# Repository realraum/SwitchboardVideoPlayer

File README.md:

# Switchboard Video Player

Use a manual telephone switchboard to select videos shown on a screen in a museum for example

## Sources:

https://github.com/labtroll/KiCad-DesignRules

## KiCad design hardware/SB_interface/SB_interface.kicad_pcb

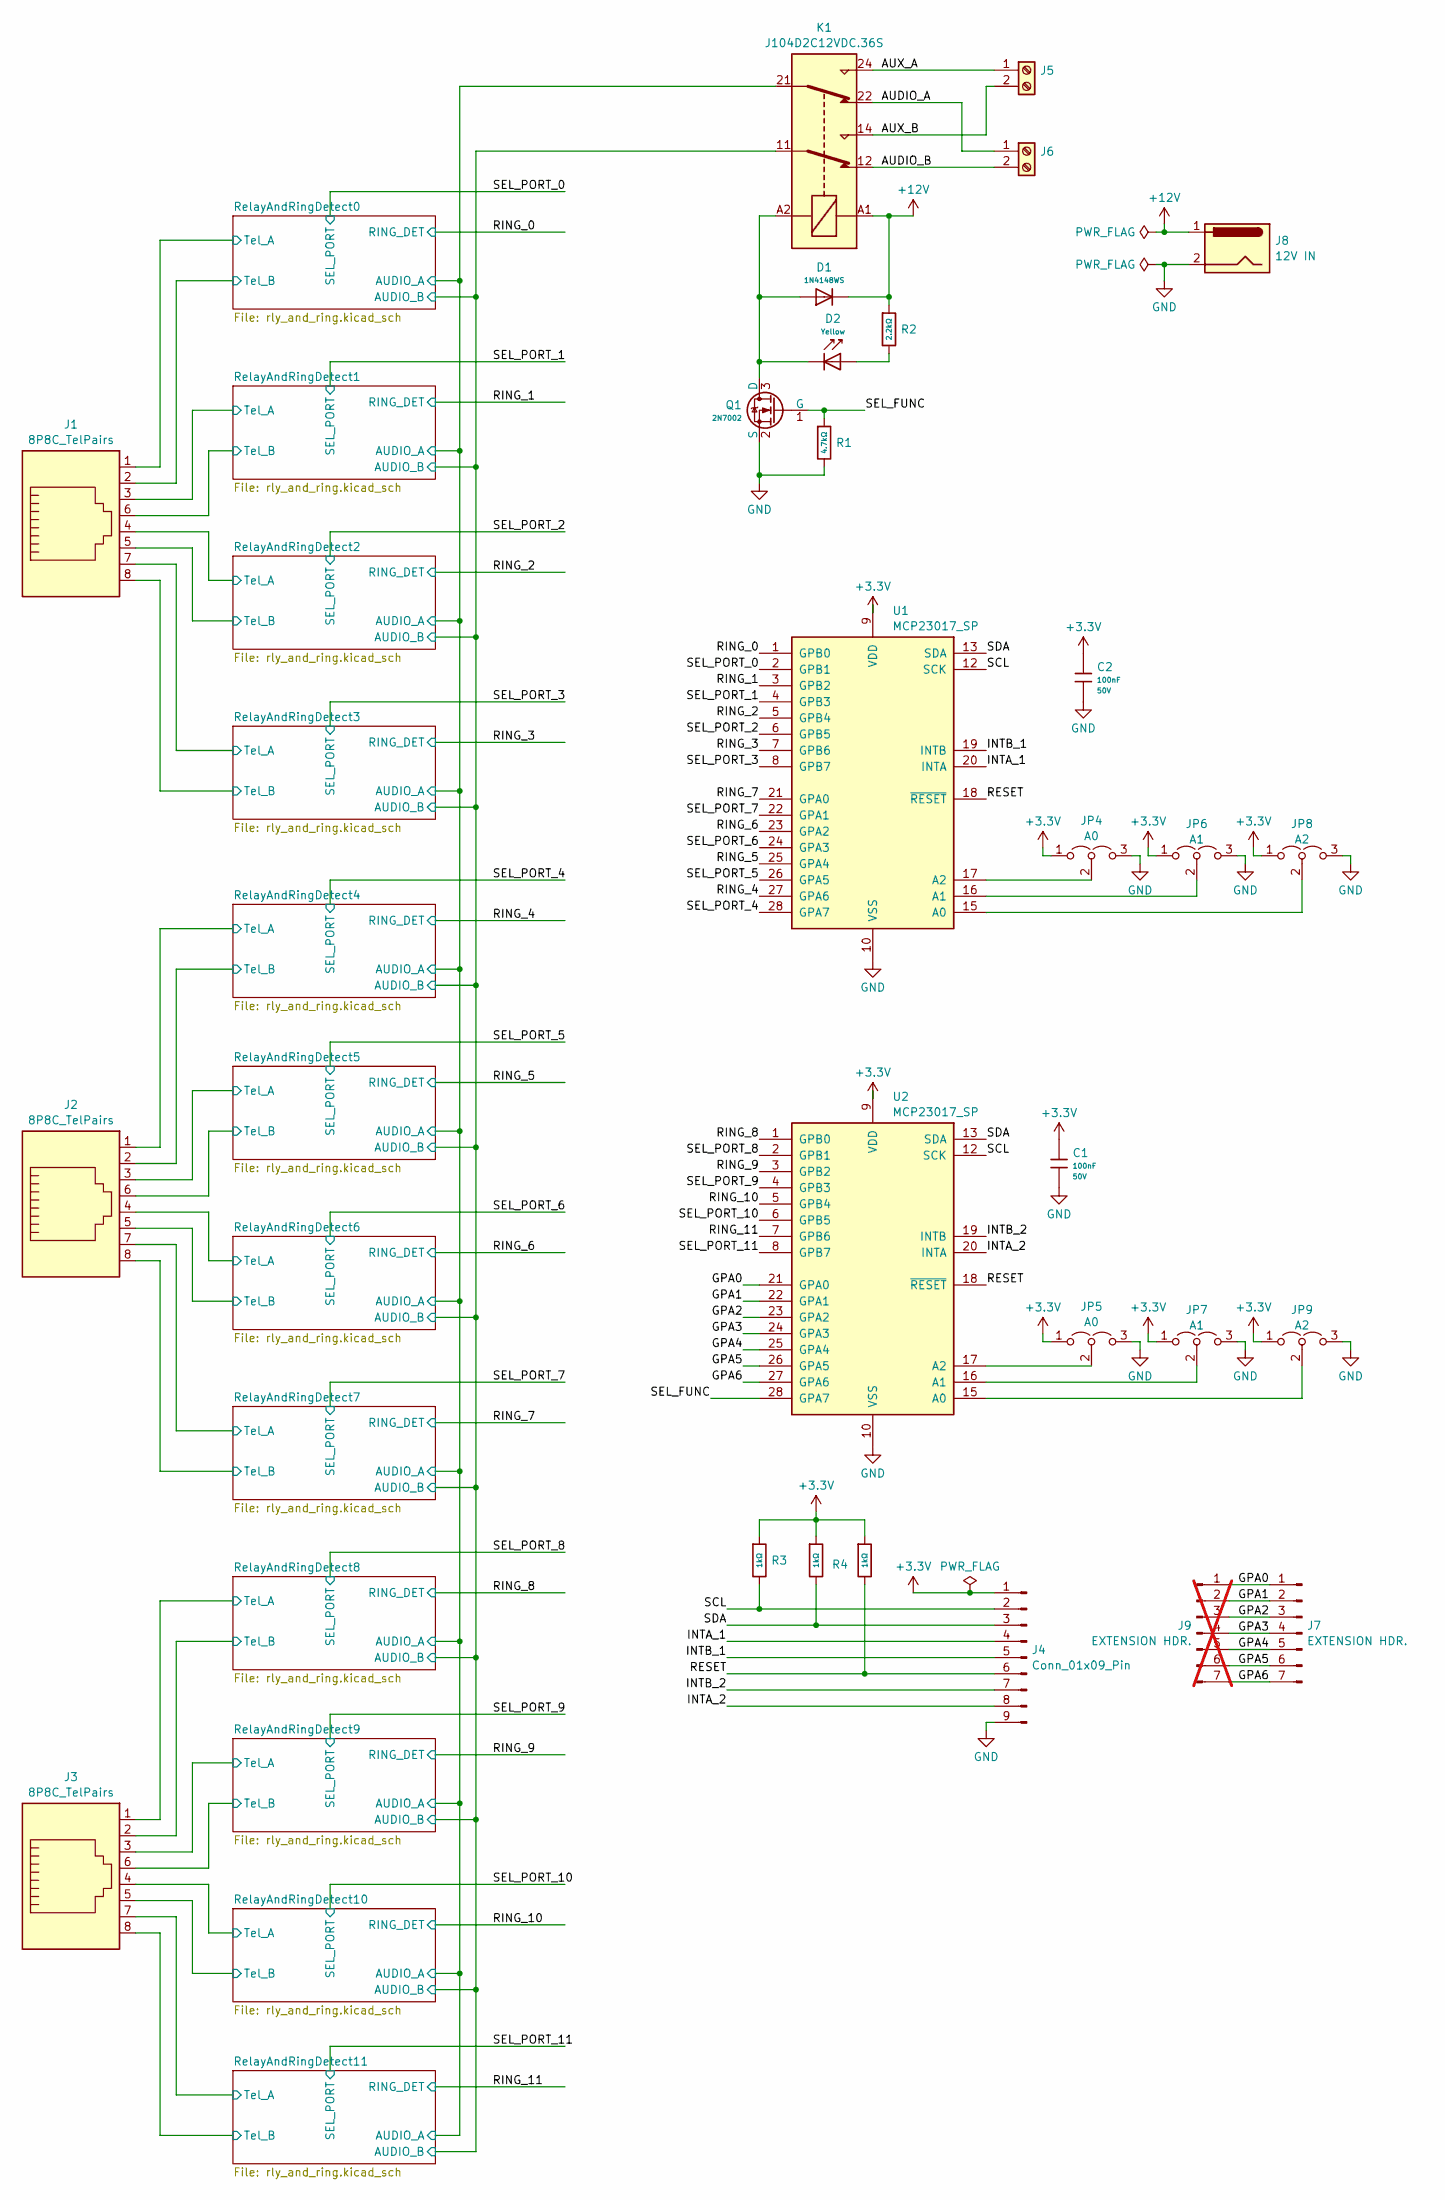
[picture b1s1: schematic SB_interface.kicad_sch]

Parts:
C1, C2: 100nF; C_0805; Voltage Rated 50V; Tolerance ±10%; Part CC0805KRX7R9BB104; LCSC C49678
D1: 1N4148WS; D_SOD-323; Forward Voltage (Vf@If) 1.25V@150mA; Reverse Voltage (Vr) 100V; Part 1N4148WS; LCSC C2128
D2: Yellow; D_0805; Part KT-0805Y; LCSC C2296
J1, J2, J3: 8P8C_TelPairs; RJ45_Amphenol_54602-x08_Horizontal
J4: Conn_01x09_Pin; PinHeader_1x09_P2.54mm_Vertical
J5: AUX; TerminalBlock_Phoenix_PT-1,5-2-3.5-H_1x02_P3.50mm_Horizontal
J6: AUDIO; TerminalBlock_Phoenix_PT-1,5-2-3.5-H_1x02_P3.50mm_Horizontal
J7: EXTENSION HDR.; PinHeader_1x07_P2.54mm_Vertical
J8: 12V IN; BarrelJack_Horizontal
J9: EXTENSION HDR.; PinHeader_1x07_P2.54mm_Vertical; not fitted
JP4, JP5: A0; PinHeader_1x03_P2.54mm_Vertical
JP6, JP7: A1; PinHeader_1x03_P2.54mm_Vertical
JP8, JP9: A2; PinHeader_1x03_P2.54mm_Vertical
K1: J104D2C12VDC.36S
Q1: 2N7002; Q_SOT-23; Part 2N7002; LCSC C8545
R1: 4.7kΩ; R_0805; Overload Voltage (Max) 150V; Tolerance ±1%; Part 0805W8F4701T5E; LCSC C17673
R2: 2.2kΩ; R_0805; Overload Voltage (Max) 150V; Tolerance ±1%; Part 0805W8F2201T5E; LCSC C17520
R3, R4, R5: 1kΩ; R_0805; Overload Voltage (Max) 150V; Tolerance ±1%; Part 0805W8F1001T5E; LCSC C17513
U1, U2: MCP23017_SP; DIP-28_W7.62mm

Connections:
+3.3V: C1.1, C2.1, J4.1, JP4.1 (A), JP5.1 (A), JP6.1 (A), JP7.1 (A), JP8.1 (A), JP9.1 (A), R3.1, R4.1, R5.1, U1.9 (VDD), U2.9 (VDD); also elsewhere on the board
+12V: D1.1, J8.1, K1.A1, R2.1; also elsewhere on the board
/AUDIO_A: J6.1, K1.22
/AUDIO_B: J6.2, K1.12
/AUX_A: J5.1, K1.24
/AUX_B: J5.2, K1.14
/GPA0: J7.1, J9.1, U2.21 (GPA0)
/GPA1: J7.2, J9.2, U2.22 (GPA1)
/GPA2: J7.3, J9.3, U2.23 (GPA2)
/GPA3: J7.4, J9.4, U2.24 (GPA3)
/GPA4: J7.5, J9.5, U2.25 (GPA4)
/GPA5: J7.6, J9.6, U2.26 (GPA5)
/GPA6: J7.7, J9.7, U2.27 (GPA6)
/INTA_1: J4.4, U1.20 (INTA)
/INTA_2: J4.8, U2.20 (INTA)
/INTB_1: J4.5, U1.19 (INTB)
/INTB_2: J4.7, U2.19 (INTB)
/RESET: J4.6, R5.2, U1.18 (~RESET), U2.18 (~RESET)
/RING_0: U1.1 (GPB0); also elsewhere on the board
/RING_1: U1.3 (GPB2); also elsewhere on the board
/RING_2: U1.5 (GPB4); also elsewhere on the board
/RING_3: U1.7 (GPB6); also elsewhere on the board
/RING_4: U1.27 (GPA6); also elsewhere on the board
/RING_5: U1.25 (GPA4); also elsewhere on the board
/RING_6: U1.23 (GPA2); also elsewhere on the board
/RING_7: U1.21 (GPA0); also elsewhere on the board
/RING_8: U2.1 (GPB0); also elsewhere on the board
/RING_9: U2.3 (GPB2); also elsewhere on the board
/RING_10: U2.5 (GPB4); also elsewhere on the board
/RING_11: U2.7 (GPB6); also elsewhere on the board
/RelayAndRingDetect0/AUDIO_A: K1.21; also elsewhere on the board
/RelayAndRingDetect0/AUDIO_B: K1.11; also elsewhere on the board
/RelayAndRingDetect0/Tel_A: J1.1; also elsewhere on the board
/RelayAndRingDetect0/Tel_B: J1.2; also elsewhere on the board
/RelayAndRingDetect1/Tel_A: J1.3; also elsewhere on the board
/RelayAndRingDetect1/Tel_B: J1.6; also elsewhere on the board
/RelayAndRingDetect2/Tel_A: J1.4; also elsewhere on the board
/RelayAndRingDetect2/Tel_B: J1.5; also elsewhere on the board
/RelayAndRingDetect3/Tel_A: J1.7; also elsewhere on the board
/RelayAndRingDetect3/Tel_B: J1.8; also elsewhere on the board
/RelayAndRingDetect4/Tel_A: J2.1; also elsewhere on the board
/RelayAndRingDetect4/Tel_B: J2.2; also elsewhere on the board
/RelayAndRingDetect5/Tel_A: J2.3; also elsewhere on the board
/RelayAndRingDetect5/Tel_B: J2.6; also elsewhere on the board
/RelayAndRingDetect6/Tel_A: J2.4; also elsewhere on the board
/RelayAndRingDetect6/Tel_B: J2.5; also elsewhere on the board
/RelayAndRingDetect7/Tel_A: J2.7; also elsewhere on the board
/RelayAndRingDetect7/Tel_B: J2.8; also elsewhere on the board
/RelayAndRingDetect8/Tel_A: J3.1; also elsewhere on the board
/RelayAndRingDetect8/Tel_B: J3.2; also elsewhere on the board
/RelayAndRingDetect9/Tel_A: J3.3; also elsewhere on the board
/RelayAndRingDetect9/Tel_B: J3.6; also elsewhere on the board
/RelayAndRingDetect10/Tel_A: J3.4; also elsewhere on the board
/RelayAndRingDetect10/Tel_B: J3.5; also elsewhere on the board
/RelayAndRingDetect11/Tel_A: J3.7; also elsewhere on the board
/RelayAndRingDetect11/Tel_B: J3.8; also elsewhere on the board
/SCL: J4.2, R3.2, U1.12 (SCK), U2.12 (SCK)
/SDA: J4.3, R4.2, U1.13 (SDA), U2.13 (SDA)
/SEL_FUNC: Q1.1 (G), R1.1, U2.28 (GPA7)
/SEL_PORT_0: U1.2 (GPB1); also elsewhere on the board
/SEL_PORT_1: U1.4 (GPB3); also elsewhere on the board
/SEL_PORT_2: U1.6 (GPB5); also elsewhere on the board
/SEL_PORT_3: U1.8 (GPB7); also elsewhere on the board
/SEL_PORT_4: U1.28 (GPA7); also elsewhere on the board
/SEL_PORT_5: U1.26 (GPA5); also elsewhere on the board
/SEL_PORT_6: U1.24 (GPA3); also elsewhere on the board
/SEL_PORT_7: U1.22 (GPA1); also elsewhere on the board
/SEL_PORT_8: U2.2 (GPB1); also elsewhere on the board
/SEL_PORT_9: U2.4 (GPB3); also elsewhere on the board
/SEL_PORT_10: U2.6 (GPB5); also elsewhere on the board
/SEL_PORT_11: U2.8 (GPB7); also elsewhere on the board
GND: C1.2, C2.2, J4.9, J8.2, JP4.3 (B), JP5.3 (B), JP6.3 (B), JP7.3 (B), JP8.3 (B), JP9.3 (B), Q1.2 (S), R1.2, U1.10 (VSS), U2.10 (VSS); also elsewhere on the board
unnamed: D2.2, R2.2
unnamed: JP4.2 (C), U1.17 (A2)
unnamed: JP5.2 (C), U2.17 (A2)
unnamed: JP6.2 (C), U1.16 (A1)
unnamed: JP7.2 (C), U2.16 (A1)
unnamed: JP8.2 (C), U1.15 (A0)
unnamed: JP9.2 (C), U2.15 (A0)
unnamed: D1.2, D2.1, K1.A2, Q1.3 (D)

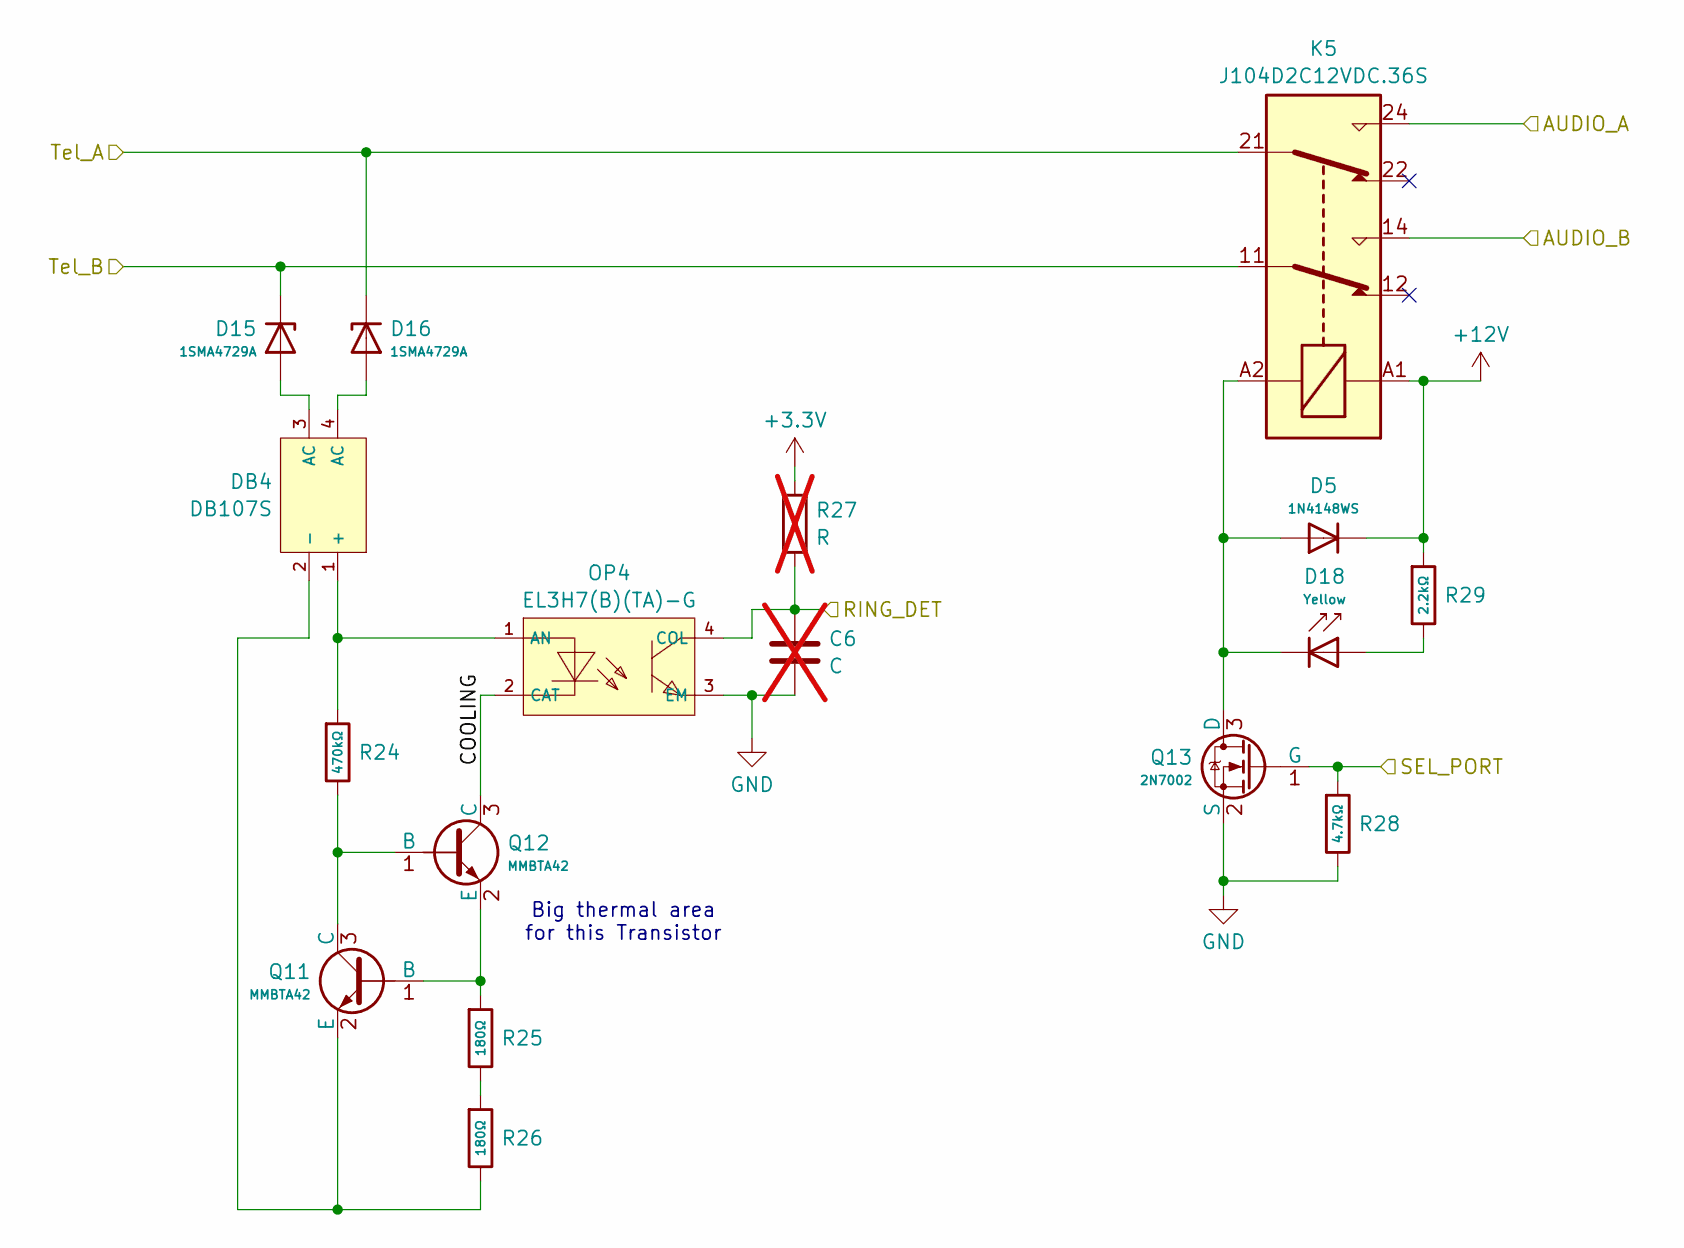
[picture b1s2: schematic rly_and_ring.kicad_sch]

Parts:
C6: C; C_0805_2012Metric_Pad1.18x1.45mm_HandSolder; not fitted
D5: 1N4148WS; D_SOD-323; Forward Voltage (Vf@If) 1.25V@150mA; Reverse Voltage (Vr) 100V; Part 1N4148WS; LCSC C2128
D15, D16: 1SMA4729A; D_SMA; Part 1SMA4729A; LCSC C19077475
D18: Yellow; D_0805; Part KT-0805Y; LCSC C2296
DB4: DB107S; DBS_L8.2-W6.4-P5.10-LS10.0-BL; Reverse Voltage (Vr) 1kV; Forward Voltage (Vf@If) 1.1V@1A; Part DB107S; LCSC C5377
K5: J104D2C12VDC.36S
OP4: EL3H7(B)(TA)-G; SOP-4_L4.4-W2.8-P1.27-LS7.0-TL; Forward Voltage 1.2V; Reverse Voltage 6V; Part EL3H7(B)(TA)-G; LCSC C32565
Q11, Q12: MMBTA42; Q_SOT-23; Part MMBTA42; LCSC C20069138
Q13: 2N7002; Q_SOT-23; Part 2N7002; LCSC C8545
R24: 470kΩ; R_0805; Overload Voltage (Max) 150V; Tolerance ±1%; Part 0805W8F4703T5E; LCSC C17709
R25, R26: 180Ω; R_2010; Part FRC2010J181 TS; LCSC C2907560
R27: R; R_0805_2012Metric_Pad1.20x1.40mm_HandSolder; not fitted
R28: 4.7kΩ; R_0805; Overload Voltage (Max) 150V; Tolerance ±1%; Part 0805W8F4701T5E; LCSC C17673
R29: 2.2kΩ; R_0805; Overload Voltage (Max) 150V; Tolerance ±1%; Part 0805W8F2201T5E; LCSC C17520

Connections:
+3.3V: R27.1; also elsewhere on the board
+12V: D5.1, K5.A1, R29.1; also elsewhere on the board
/RING_3: C6.1, OP4.4 (COL), R27.2; also elsewhere on the board
/RelayAndRingDetect0/AUDIO_A: K5.24; also elsewhere on the board
/RelayAndRingDetect0/AUDIO_B: K5.14; also elsewhere on the board
/RelayAndRingDetect3/COOLING: OP4.2 (CAT), Q12.3 (C)
/RelayAndRingDetect3/Tel_A: D16.1, K5.21; also elsewhere on the board
/RelayAndRingDetect3/Tel_B: D15.1, K5.11; also elsewhere on the board
/SEL_PORT_3: Q13.1 (G), R28.1; also elsewhere on the board
GND: C6.2, OP4.3 (EM), Q13.2 (S), R28.2; also elsewhere on the board
unnamed: D15.2, DB4.3 (AC)
unnamed: D16.2, DB4.4 (AC)
unnamed: D18.2, R29.2
unnamed: DB4.1 (+), OP4.1 (AN), R24.1
unnamed: DB4.2 (-), Q11.2 (E), R26.2
unnamed: Q11.1 (B), Q12.2 (E), R25.1
unnamed: Q11.3 (C), Q12.1 (B), R24.2
unnamed: R25.2, R26.1

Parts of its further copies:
C3, C4, C5, C7, C8, C9, C10, C11, C12, C13, C14: C; C_0805_2012Metric_Pad1.18x1.45mm_HandSolder; not fitted
D3, D4, D7, D8, D11, D12, D19, D20, D23, D24, D27, D28, D31, D32, D35, D36, D39, D40, D43, D44, D47, D48: 1SMA4729A; D_SMA; Part 1SMA4729A; LCSC C19077475
D6, D10, D14, D22, D26, D30, D34, D38, D42, D46, D50: Yellow; D_0805; Part KT-0805Y; LCSC C2296
D9, D13, D17, D21, D25, D29, D33, D37, D41, D45, D49: 1N4148WS; D_SOD-323; Forward Voltage (Vf@If) 1.25V@150mA; Reverse Voltage (Vr) 100V; Part 1N4148WS; LCSC C2128
DB1, DB2, DB3, DB5, DB6, DB7, DB8, DB9, DB10, DB11, DB12: DB107S; DBS_L8.2-W6.4-P5.10-LS10.0-BL; Reverse Voltage (Vr) 1kV; Forward Voltage (Vf@If) 1.1V@1A; Part DB107S; LCSC C5377
K2, K3, K4, K6, K7, K8, K9, K10, K11, K12, K13: J104D2C12VDC.36S
OP1, OP2, OP3, OP5, OP6, OP7, OP8, OP9, OP10, OP11, OP12: EL3H7(B)(TA)-G; SOP-4_L4.4-W2.8-P1.27-LS7.0-TL; Forward Voltage 1.2V; Reverse Voltage 6V; Part EL3H7(B)(TA)-G; LCSC C32565
Q2, Q3, Q5, Q6, Q8, Q9, Q14, Q15, Q17, Q18, Q20, Q21, Q23, Q24, Q26, Q27, Q29, Q30, Q32, Q33, Q35, Q36: MMBTA42; Q_SOT-23; Part MMBTA42; LCSC C20069138
Q4, Q7, Q10, Q16, Q19, Q22, Q25, Q28, Q31, Q34, Q37: 2N7002; Q_SOT-23; Part 2N7002; LCSC C8545
R6, R12, R18, R30, R36, R42, R48, R54, R60, R66, R72: 470kΩ; R_0805; Overload Voltage (Max) 150V; Tolerance ±1%; Part 0805W8F4703T5E; LCSC C17709
R7, R8, R13, R14, R19, R20, R31, R32, R37, R38, R43, R44, R49, R50, R55, R56, R61, R62, R67, R68, R73, R74: 180Ω; R_2010; Part FRC2010J181 TS; LCSC C2907560
R9, R15, R21, R33, R39, R45, R51, R57, R63, R69, R75: R; R_0805_2012Metric_Pad1.20x1.40mm_HandSolder; not fitted
R10, R16, R22, R34, R40, R46, R52, R58, R64, R70, R76: 4.7kΩ; R_0805; Overload Voltage (Max) 150V; Tolerance ±1%; Part 0805W8F4701T5E; LCSC C17673
R11, R17, R23, R35, R41, R47, R53, R59, R65, R71, R77: 2.2kΩ; R_0805; Overload Voltage (Max) 150V; Tolerance ±1%; Part 0805W8F2201T5E; LCSC C17520

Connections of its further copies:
+3.3V: R9.1, R15.1, R21.1, R33.1, R39.1, R45.1, R51.1, R57.1, R63.1, R69.1, R75.1; also elsewhere on the board
+12V: D9.1, D13.1, D17.1, D21.1, D25.1, D29.1, D33.1, D37.1, D41.1, D45.1, D49.1, K2.A1, K3.A1, K4.A1, K6.A1, K7.A1, K8.A1, K9.A1, K10.A1, K11.A1, K12.A1, K13.A1, R11.1, R17.1, R23.1, R35.1, R41.1, R47.1, R53.1, R59.1, R65.1, R71.1, R77.1; also elsewhere on the board
/RING_0: C4.1, OP2.4 (COL), R15.2; also elsewhere on the board
/RING_1: C3.1, OP1.4 (COL), R9.2; also elsewhere on the board
/RING_2: C5.1, OP3.4 (COL), R21.2; also elsewhere on the board
/RING_4: C7.1, OP5.4 (COL), R33.2; also elsewhere on the board
/RING_5: C8.1, OP6.4 (COL), R39.2; also elsewhere on the board
/RING_6: C9.1, OP7.4 (COL), R45.2; also elsewhere on the board
/RING_7: C10.1, OP8.4 (COL), R51.2; also elsewhere on the board
/RING_8: C11.1, OP9.4 (COL), R57.2; also elsewhere on the board
/RING_9: C12.1, OP10.4 (COL), R63.2; also elsewhere on the board
/RING_10: C13.1, OP11.4 (COL), R69.2; also elsewhere on the board
/RING_11: C14.1, OP12.4 (COL), R75.2; also elsewhere on the board
/RelayAndRingDetect0/AUDIO_A: K2.24, K3.24, K4.24, K6.24, K7.24, K8.24, K9.24, K10.24, K11.24, K12.24, K13.24; also elsewhere on the board
/RelayAndRingDetect0/AUDIO_B: K2.14, K3.14, K4.14, K6.14, K7.14, K8.14, K9.14, K10.14, K11.14, K12.14, K13.14; also elsewhere on the board
/RelayAndRingDetect0/COOLING: OP2.2 (CAT), Q6.3 (C)
/RelayAndRingDetect0/Tel_A: D8.1, K3.21; also elsewhere on the board
/RelayAndRingDetect0/Tel_B: D7.1, K3.11; also elsewhere on the board
/RelayAndRingDetect1/COOLING: OP1.2 (CAT), Q3.3 (C)
/RelayAndRingDetect1/Tel_A: D4.1, K2.21; also elsewhere on the board
/RelayAndRingDetect1/Tel_B: D3.1, K2.11; also elsewhere on the board
/RelayAndRingDetect2/COOLING: OP3.2 (CAT), Q9.3 (C)
/RelayAndRingDetect2/Tel_A: D12.1, K4.21; also elsewhere on the board
/RelayAndRingDetect2/Tel_B: D11.1, K4.11; also elsewhere on the board
/RelayAndRingDetect4/COOLING: OP5.2 (CAT), Q15.3 (C)
/RelayAndRingDetect4/Tel_A: D20.1, K6.21; also elsewhere on the board
/RelayAndRingDetect4/Tel_B: D19.1, K6.11; also elsewhere on the board
/RelayAndRingDetect5/COOLING: OP6.2 (CAT), Q18.3 (C)
/RelayAndRingDetect5/Tel_A: D24.1, K7.21; also elsewhere on the board
/RelayAndRingDetect5/Tel_B: D23.1, K7.11; also elsewhere on the board
/RelayAndRingDetect6/COOLING: OP7.2 (CAT), Q21.3 (C)
/RelayAndRingDetect6/Tel_A: D28.1, K8.21; also elsewhere on the board
/RelayAndRingDetect6/Tel_B: D27.1, K8.11; also elsewhere on the board
/RelayAndRingDetect7/COOLING: OP8.2 (CAT), Q24.3 (C)
/RelayAndRingDetect7/Tel_A: D32.1, K9.21; also elsewhere on the board
/RelayAndRingDetect7/Tel_B: D31.1, K9.11; also elsewhere on the board
/RelayAndRingDetect8/COOLING: OP9.2 (CAT), Q27.3 (C)
/RelayAndRingDetect8/Tel_A: D36.1, K10.21; also elsewhere on the board
/RelayAndRingDetect8/Tel_B: D35.1, K10.11; also elsewhere on the board
/RelayAndRingDetect9/COOLING: OP10.2 (CAT), Q30.3 (C)
/RelayAndRingDetect9/Tel_A: D40.1, K11.21; also elsewhere on the board
/RelayAndRingDetect9/Tel_B: D39.1, K11.11; also elsewhere on the board
/RelayAndRingDetect10/COOLING: OP11.2 (CAT), Q33.3 (C)
/RelayAndRingDetect10/Tel_A: D44.1, K12.21; also elsewhere on the board
/RelayAndRingDetect10/Tel_B: D43.1, K12.11; also elsewhere on the board
/RelayAndRingDetect11/COOLING: OP12.2 (CAT), Q36.3 (C)
/RelayAndRingDetect11/Tel_A: D48.1, K13.21; also elsewhere on the board
/RelayAndRingDetect11/Tel_B: D47.1, K13.11; also elsewhere on the board
/SEL_PORT_0: Q7.1 (G), R16.1; also elsewhere on the board
/SEL_PORT_1: Q4.1 (G), R10.1; also elsewhere on the board
/SEL_PORT_2: Q10.1 (G), R22.1; also elsewhere on the board
/SEL_PORT_4: Q16.1 (G), R34.1; also elsewhere on the board
/SEL_PORT_5: Q19.1 (G), R40.1; also elsewhere on the board
/SEL_PORT_6: Q22.1 (G), R46.1; also elsewhere on the board
/SEL_PORT_7: Q25.1 (G), R52.1; also elsewhere on the board
/SEL_PORT_8: Q28.1 (G), R58.1; also elsewhere on the board
/SEL_PORT_9: Q31.1 (G), R64.1; also elsewhere on the board
/SEL_PORT_10: Q34.1 (G), R70.1; also elsewhere on the board
/SEL_PORT_11: Q37.1 (G), R76.1; also elsewhere on the board
GND: C3.2, C4.2, C5.2, C7.2, C8.2, C9.2, C10.2, C11.2, C12.2, C13.2, C14.2, OP1.3 (EM), OP2.3 (EM), OP3.3 (EM), OP5.3 (EM), OP6.3 (EM), OP7.3 (EM), OP8.3 (EM), OP9.3 (EM), OP10.3 (EM), OP11.3 (EM), OP12.3 (EM), Q4.2 (S), Q7.2 (S), Q10.2 (S), Q16.2 (S), Q19.2 (S), Q22.2 (S), Q25.2 (S), Q28.2 (S), Q31.2 (S), Q34.2 (S), Q37.2 (S), R10.2, R16.2, R22.2, R34.2, R40.2, R46.2, R52.2, R58.2, R64.2, R70.2, R76.2; also elsewhere on the board
unnamed: D3.2, DB1.3 (AC)
unnamed: D4.2, DB1.4 (AC)
unnamed: D6.2, R11.2
unnamed: D7.2, DB2.3 (AC)
unnamed: D8.2, DB2.4 (AC)
unnamed: D10.2, R17.2
unnamed: D11.2, DB3.3 (AC)
unnamed: D12.2, DB3.4 (AC)
unnamed: D14.2, R23.2
unnamed: D19.2, DB5.3 (AC)
unnamed: D20.2, DB5.4 (AC)
unnamed: D22.2, R35.2
unnamed: D23.2, DB6.3 (AC)
unnamed: D24.2, DB6.4 (AC)
unnamed: D26.2, R41.2
unnamed: D27.2, DB7.3 (AC)
unnamed: D28.2, DB7.4 (AC)
unnamed: D30.2, R47.2
unnamed: D31.2, DB8.3 (AC)
unnamed: D32.2, DB8.4 (AC)
unnamed: D34.2, R53.2
unnamed: D35.2, DB9.3 (AC)
unnamed: D36.2, DB9.4 (AC)
unnamed: D38.2, R59.2
unnamed: D39.2, DB10.3 (AC)
unnamed: D40.2, DB10.4 (AC)
unnamed: D42.2, R65.2
unnamed: D43.2, DB11.3 (AC)
unnamed: D44.2, DB11.4 (AC)
unnamed: D46.2, R71.2
unnamed: D47.2, DB12.3 (AC)
unnamed: D48.2, DB12.4 (AC)
unnamed: D50.2, R77.2
unnamed: DB1.1 (+), OP1.1 (AN), R6.1
unnamed: DB1.2 (-), Q2.2 (E), R8.2
unnamed: DB2.1 (+), OP2.1 (AN), R12.1
unnamed: DB2.2 (-), Q5.2 (E), R14.2
unnamed: DB3.1 (+), OP3.1 (AN), R18.1
unnamed: DB3.2 (-), Q8.2 (E), R20.2
unnamed: DB5.1 (+), OP5.1 (AN), R30.1
unnamed: DB5.2 (-), Q14.2 (E), R32.2
unnamed: DB6.1 (+), OP6.1 (AN), R36.1
unnamed: DB6.2 (-), Q17.2 (E), R38.2
unnamed: DB7.1 (+), OP7.1 (AN), R42.1
unnamed: DB7.2 (-), Q20.2 (E), R44.2
unnamed: DB8.1 (+), OP8.1 (AN), R48.1
unnamed: DB8.2 (-), Q23.2 (E), R50.2
unnamed: DB9.1 (+), OP9.1 (AN), R54.1
unnamed: DB9.2 (-), Q26.2 (E), R56.2
unnamed: DB10.1 (+), OP10.1 (AN), R60.1
unnamed: DB10.2 (-), Q29.2 (E), R62.2
unnamed: DB11.1 (+), OP11.1 (AN), R66.1
unnamed: DB11.2 (-), Q32.2 (E), R68.2
unnamed: DB12.1 (+), OP12.1 (AN), R72.1
unnamed: DB12.2 (-), Q35.2 (E), R74.2
unnamed: Q2.1 (B), Q3.2 (E), R7.1
unnamed: Q2.3 (C), Q3.1 (B), R6.2
unnamed: Q5.1 (B), Q6.2 (E), R13.1
unnamed: Q5.3 (C), Q6.1 (B), R12.2
unnamed: D9.2, D10.1, K3.A2, Q7.3 (D)
unnamed: Q8.1 (B), Q9.2 (E), R19.1
unnamed: Q8.3 (C), Q9.1 (B), R18.2
unnamed: D13.2, D14.1, K4.A2, Q10.3 (D)
unnamed: Q14.1 (B), Q15.2 (E), R31.1
unnamed: Q14.3 (C), Q15.1 (B), R30.2
unnamed: D21.2, D22.1, K6.A2, Q16.3 (D)
unnamed: Q17.1 (B), Q18.2 (E), R37.1
unnamed: Q17.3 (C), Q18.1 (B), R36.2
unnamed: D25.2, D26.1, K7.A2, Q19.3 (D)
unnamed: Q20.1 (B), Q21.2 (E), R43.1
unnamed: Q20.3 (C), Q21.1 (B), R42.2
unnamed: D29.2, D30.1, K8.A2, Q22.3 (D)
unnamed: Q23.1 (B), Q24.2 (E), R49.1
unnamed: Q23.3 (C), Q24.1 (B), R48.2
unnamed: D33.2, D34.1, K9.A2, Q25.3 (D)
unnamed: Q26.1 (B), Q27.2 (E), R55.1
unnamed: Q26.3 (C), Q27.1 (B), R54.2
unnamed: D37.2, D38.1, K10.A2, Q28.3 (D)
unnamed: Q29.1 (B), Q30.2 (E), R61.1
unnamed: Q29.3 (C), Q30.1 (B), R60.2
unnamed: D41.2, D42.1, K11.A2, Q31.3 (D)
unnamed: Q32.1 (B), Q33.2 (E), R67.1
unnamed: Q32.3 (C), Q33.1 (B), R66.2
unnamed: D45.2, D46.1, K12.A2, Q34.3 (D)
unnamed: Q35.1 (B), Q36.2 (E), R73.1
unnamed: Q35.3 (C), Q36.1 (B), R72.2
unnamed: D49.2, D50.1, K13.A2, Q37.3 (D)
unnamed: R7.2, R8.1
unnamed: R13.2, R14.1
unnamed: R19.2, R20.1
unnamed: R31.2, R32.1
unnamed: R37.2, R38.1
unnamed: R43.2, R44.1
unnamed: R49.2, R50.1
unnamed: R55.2, R56.1
unnamed: R61.2, R62.1
unnamed: R67.2, R68.1
unnamed: R73.2, R74.1

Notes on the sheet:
Big thermal area for this Transistor

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
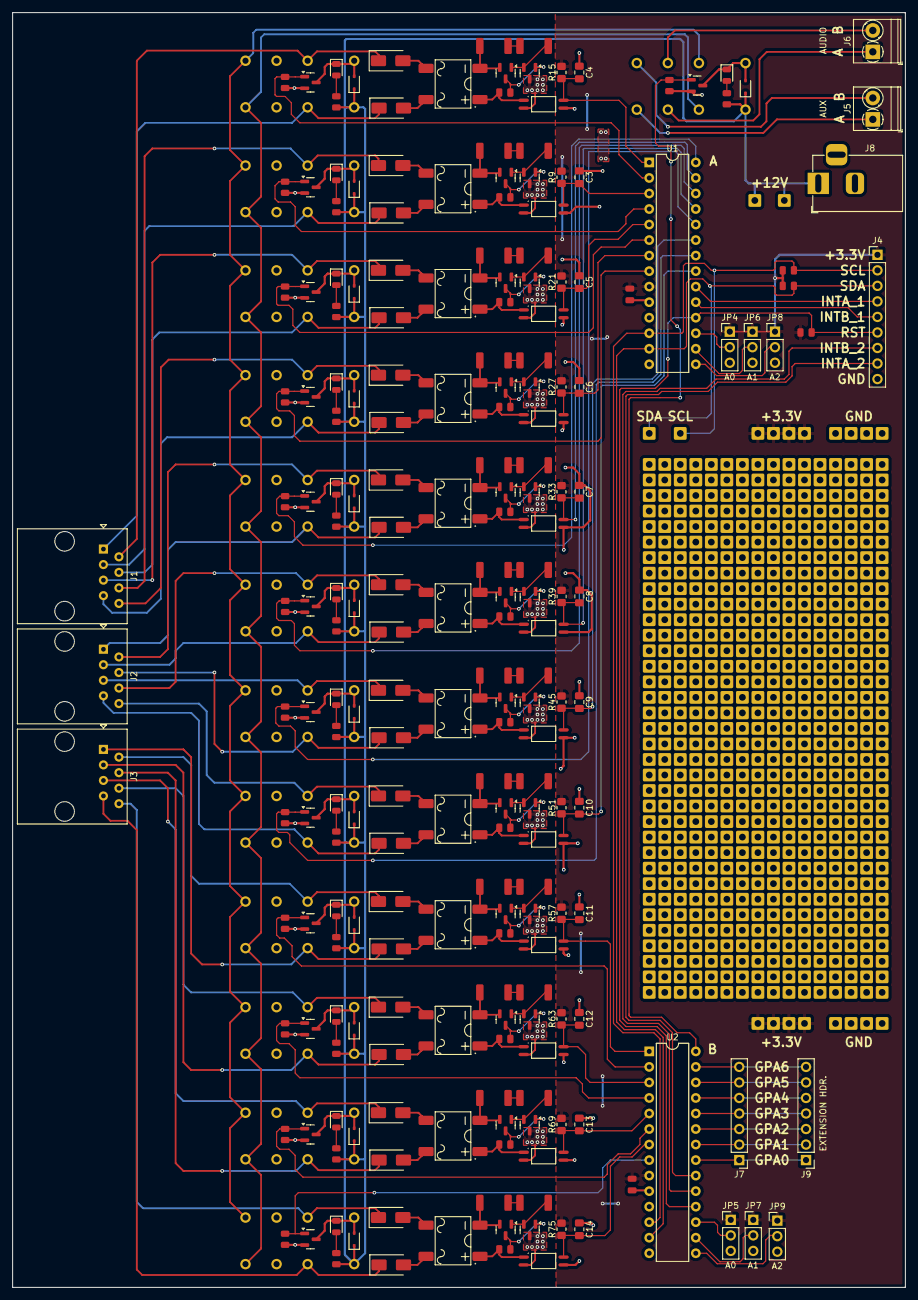
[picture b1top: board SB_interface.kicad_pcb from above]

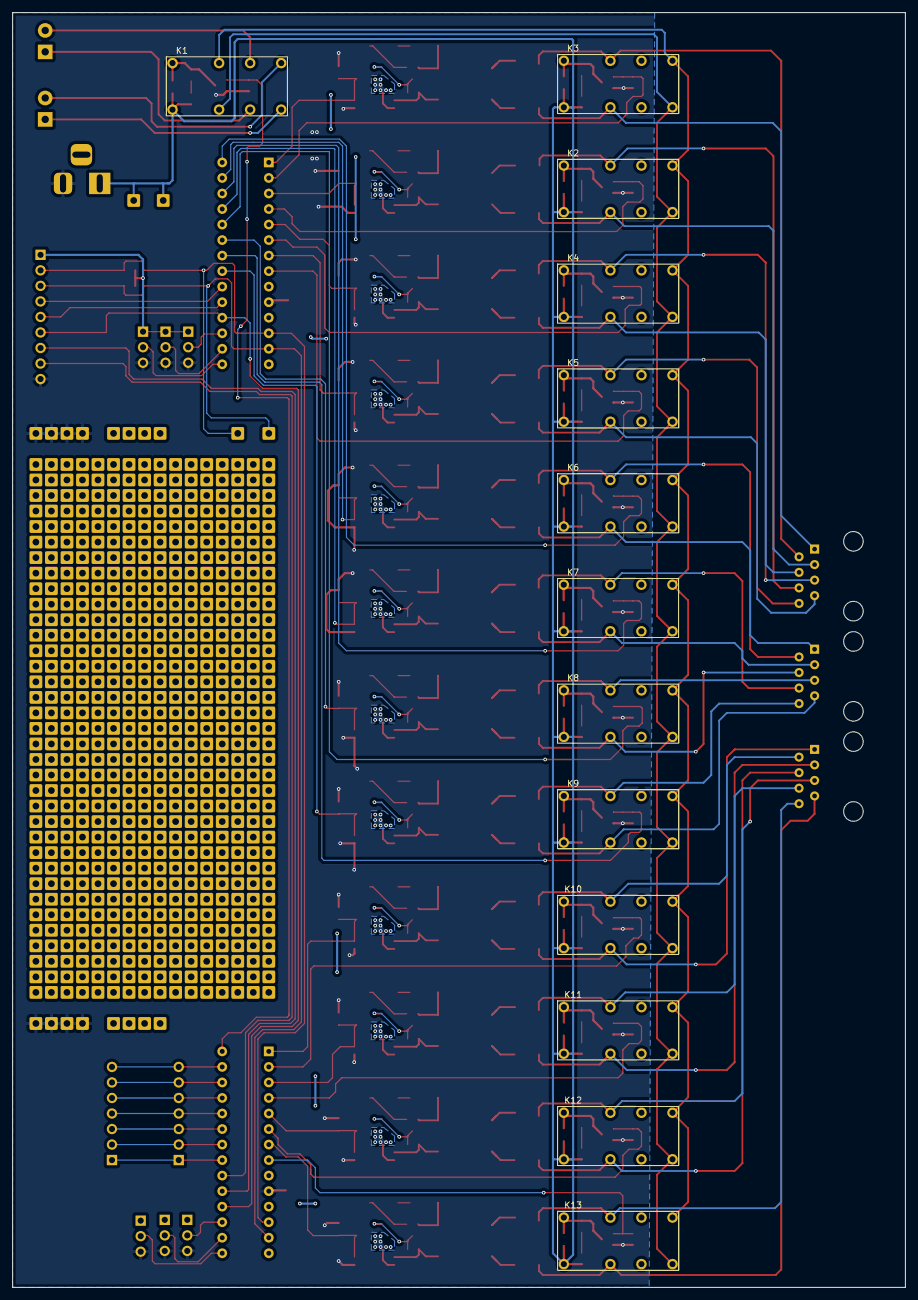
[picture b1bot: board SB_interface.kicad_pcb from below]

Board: 2 copper layers, 146.1 x 208.5 mm, 232 parts (13 on the bottom side), 200 nets.

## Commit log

2025-01-24 initial kicad project
2025-01-28 current source for ring det. + main 8p8c pinout corrected
2025-01-29 assigneld footprints + started layout
2025-01-29 replicated layout + added JLCPCB Design rules file
2025-01-29 added simulation files
2025-02-02 layout of tel inputs
2025-02-02 fixed some annotation error
2025-02-04 more layout stuff
2025-02-05 added prototyping area
